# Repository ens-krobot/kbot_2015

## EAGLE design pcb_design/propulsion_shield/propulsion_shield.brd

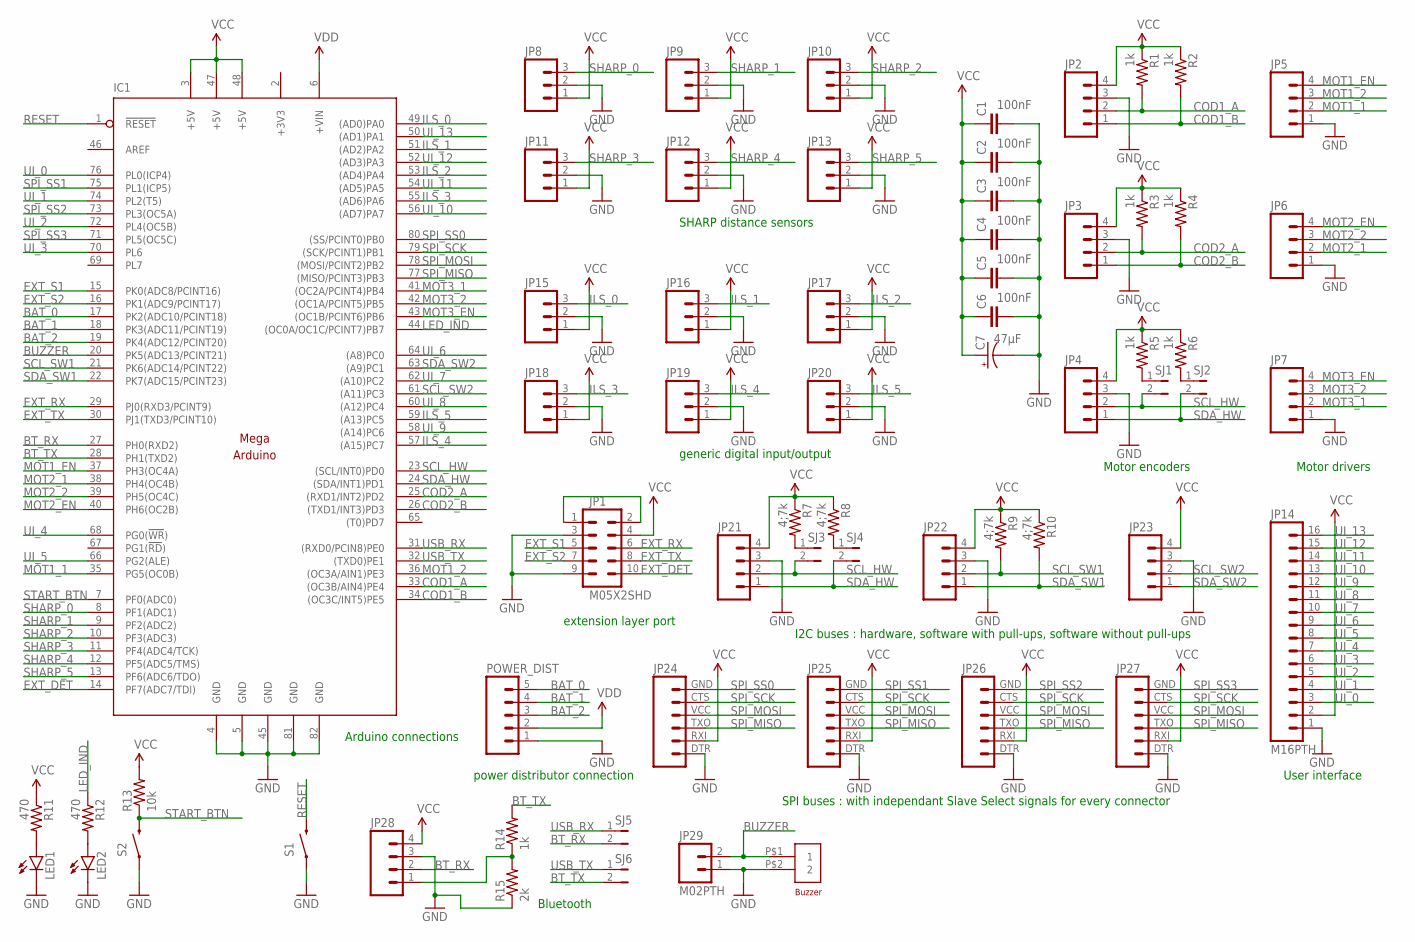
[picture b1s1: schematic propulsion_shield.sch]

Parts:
C1, C2, C3, C4, C5, C6: 100nF; 1206
C7: 47µF; PANASONIC_D
IC1: MEGAARDUINO_13; MEGA_ARDUINO_NO_HOLE
JP1: M05X2SHD; 2X5-SHROUDED
JP2, JP3, JP4, JP5, JP6, JP7, JP21, JP22, JP23, JP28: M04PTH; 1X04
JP8, JP9, JP10, JP11, JP12, JP13, JP15, JP16, JP17, JP18, JP19, JP20: M03PTH; 1X03
JP14: M16PTH; 1X16
JP24, JP25, JP26, JP27: M06SIP; 1X06
JP29: M02PTH; 1X02
LED1, LED2: LED1206; LED-1206
POWER_DIST: M05PTH; 1X05
R1, R2, R3, R4, R5, R6, R14: 1k; 1206
R7, R8, R9, R10: 4;7k; 1206
R11, R12: 470; 1206
R13: 10k; 1206
R15: 2k; 1206
S1, S2: SWITCH-MOMENTARY-2PTH; TACTILE-PTH
SJ1, SJ2, SJ3, SJ4, SJ5, SJ6: JUMPER-PTH-2-NO; PTH-JUMPER-2-NO_NO_SILK
U$1: BUZZER

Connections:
+3V3: IC1.2 (+3V3)
BAT_0: IC1.17 (PK2(ADC10/PCINT18)), POWER_DIST.5
BAT_1: IC1.18 (PK3(ADC11/PCINT19)), POWER_DIST.4
BAT_2: IC1.19 (PK4(ADC12/PCINT20)), POWER_DIST.3
BT_RX: IC1.27 (PH0(RXD2)), JP28.2, SJ5.2
BT_TX: IC1.28 (PH1(TXD2)), R14.2, SJ6.2
BUZZER: IC1.20 (PK5(ADC13/PCINT21)), JP29.2, U$1.P$1 (1)
COD1_A: IC1.33 ((OC3B/AIN4)PE4), JP2.2, R1.2
COD1_B: IC1.34 ((OC3C/INT5)PE5), JP2.1, R2.2
COD2_A: IC1.25 ((RXD1/INT2)PD2), JP3.2, R3.2
COD2_B: IC1.26 ((TXD1/INT3)PD3), JP3.1, R4.2
EXT_DET: IC1.14 (PF7(ADC7/TDI)), JP1.10
EXT_RX: IC1.29 (PJ0(RXD3/PCINT9)), JP1.6
EXT_S1: IC1.15 (PK0(ADC8/PCINT16)), JP1.5
EXT_S2: IC1.16 (PK1(ADC9/PCINT17)), JP1.7
EXT_TX: IC1.30 (PJ1(TXD3/PCINT10)), JP1.8
GND: C1.2, C2.2, C3.2, C4.2, C5.2, C6.2, C7.-, IC1.4 (GND), IC1.5 (GND), IC1.45 (GND), IC1.81 (GND), IC1.82 (GND), JP1.3, JP1.9, JP2.3, JP3.3, JP4.3, JP5.1, JP6.1, JP7.1, JP8.2, JP9.2, JP10.2, JP11.2, JP12.2, JP13.2, JP14.1, JP15.2, JP16.2, JP17.2, JP18.2, JP19.2, JP20.2, JP21.3, JP22.3, JP23.3, JP24.DTR (1), JP25.DTR (1), JP26.DTR (1), JP27.DTR (1), JP28.3, JP29.1, LED1.C, LED2.C, POWER_DIST.1, R15.1, S1.1, S2.1, U$1.P$2 (2)
ILS_0: IC1.49 ((AD0)PA0), JP15.3
ILS_1: IC1.51 ((AD2)PA2), JP16.3
ILS_2: IC1.53 ((AD4)PA4), JP17.3
ILS_3: IC1.55 ((AD6)PA6), JP18.3
ILS_4: IC1.57 ((A15)PC7), JP19.3
ILS_5: IC1.59 ((A13)PC5), JP20.3
LED_IND: IC1.44 ((OC0A/OC1C/PCINT7)PB7), R12.1
MOT1_1: IC1.35 (PG5(OC0B)), JP5.2
MOT1_2: IC1.36 ((OC3A/AIN1)PE3), JP5.3
MOT1_EN: IC1.37 (PH3(OC4A)), JP5.4
MOT2_1: IC1.38 (PH4(OC4B)), JP6.2
MOT2_2: IC1.39 (PH5(OC4C)), JP6.3
MOT2_EN: IC1.40 (PH6(OC2B)), JP6.4
MOT3_1: IC1.41 ((OC2A/PCINT4)PB4), JP7.2
MOT3_2: IC1.42 ((OC1A/PCINT5)PB5), JP7.3
MOT3_EN: IC1.43 ((OC1B/PCINT6)PB6), JP7.4
unnamed: JP1.1, JP1.2
unnamed: R7.2, SJ3.1
unnamed: R8.2, SJ4.1
unnamed: R5.2, SJ1.1
unnamed: R6.2, SJ2.1
unnamed: LED1.A, R11.2
unnamed: LED2.A, R12.2
unnamed: JP28.1, R14.1, R15.2
RESET: IC1.1 (!RESET), S1.3 (2)
SCL_HW: IC1.23 ((SCL/INT0)PD0), JP4.2, JP21.2, SJ1.2, SJ3.2
SCL_SW1: IC1.21 (PK6(ADC14/PCINT22)), JP22.2, R9.2
SCL_SW2: IC1.61 ((A11)PC3), JP23.2
SDA_HW: IC1.24 ((SDA/INT1)PD1), JP4.1, JP21.1, SJ2.2, SJ4.2
SDA_SW1: IC1.22 (PK7(ADC15/PCINT23)), JP22.1, R10.2
SDA_SW2: IC1.63 ((A9)PC1), JP23.1
SHARP_0: IC1.8 (PF1(ADC1)), JP8.3
SHARP_1: IC1.9 (PF2(ADC2)), JP9.3
SHARP_2: IC1.10 (PF3(ADC3)), JP10.3
SHARP_3: IC1.11 (PF4(ADC4/TCK)), JP11.3
SHARP_4: IC1.12 (PF5(ADC5/TMS)), JP12.3
SHARP_5: IC1.13 (PF6(ADC6/TDO)), JP13.3
SPI_MISO: IC1.77 ((MISO/PCINT3)PB3), JP24.TXO (3), JP25.TXO (3), JP26.TXO (3), JP27.TXO (3)
SPI_MOSI: IC1.78 ((MOSI/PCINT2)PB2), JP24.VCC (4), JP25.VCC (4), JP26.VCC (4), JP27.VCC (4)
SPI_SCK: IC1.79 ((SCK/PCINT1)PB1), JP24.CTS (5), JP25.CTS (5), JP26.CTS (5), JP27.CTS (5)
SPI_SS0: IC1.80 ((SS/PCINT0)PB0), JP24.GND (6)
SPI_SS1: IC1.75 (PL1(ICP5)), JP25.GND (6)
SPI_SS2: IC1.73 (PL3(OC5A)), JP26.GND (6)
SPI_SS3: IC1.71 (PL5(OC5C)), JP27.GND (6)
START_BTN: IC1.7 (PF0(ADC0)), R13.1, S2.3 (2)
UI_0: IC1.76 (PL0(ICP4)), JP14.3
UI_1: IC1.74 (PL2(T5)), JP14.4
UI_2: IC1.72 (PL4(OC5B)), JP14.5
UI_3: IC1.70 (PL6), JP14.6
UI_4: IC1.68 (PG0(!WR!)), JP14.7
UI_5: IC1.66 (PG2(ALE)), JP14.8
UI_6: IC1.64 ((A8)PC0), JP14.9
UI_7: IC1.62 ((A10)PC2), JP14.10
UI_8: IC1.60 ((A12)PC4), JP14.11
UI_9: IC1.58 ((A14)PC6), JP14.12
UI_10: IC1.56 ((AD7)PA7), JP14.13
UI_11: IC1.54 ((AD5)PA5), JP14.14
UI_12: IC1.52 ((AD3)PA3), JP14.15
UI_13: IC1.50 ((AD1)PA1), JP14.16
USB_RX: IC1.31 ((RXD0/PCIN8)PE0), SJ5.1
USB_TX: IC1.32 ((TXD0)PE1), SJ6.1
VCC: C1.1, C2.1, C3.1, C4.1, C5.1, C6.1, C7.+, IC1.3 (+5V), IC1.47 (+5V), IC1.48 (+5V), JP1.4, JP2.4, JP3.4, JP4.4, JP8.1, JP9.1, JP10.1, JP11.1, JP12.1, JP13.1, JP14.2, JP15.1, JP16.1, JP17.1, JP18.1, JP19.1, JP20.1, JP21.4, JP22.4, JP23.4, JP24.RXI (2), JP25.RXI (2), JP26.RXI (2), JP27.RXI (2), JP28.4, R1.1, R2.1, R3.1, R4.1, R5.1, R6.1, R7.1, R8.1, R9.1, R10.1, R11.1, R13.2
VDD: IC1.6 (+VIN), POWER_DIST.2

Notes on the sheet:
power distributor connection
extension layer port
Arduino connections
Motor encoders
Motor drivers
User interface
SHARP distance sensors
generic digital input/output
I2C buses : hardware, software with pull-ups, software without pull-ups
SPI buses : with independant Slave Select signals for every connector
Bluetooth

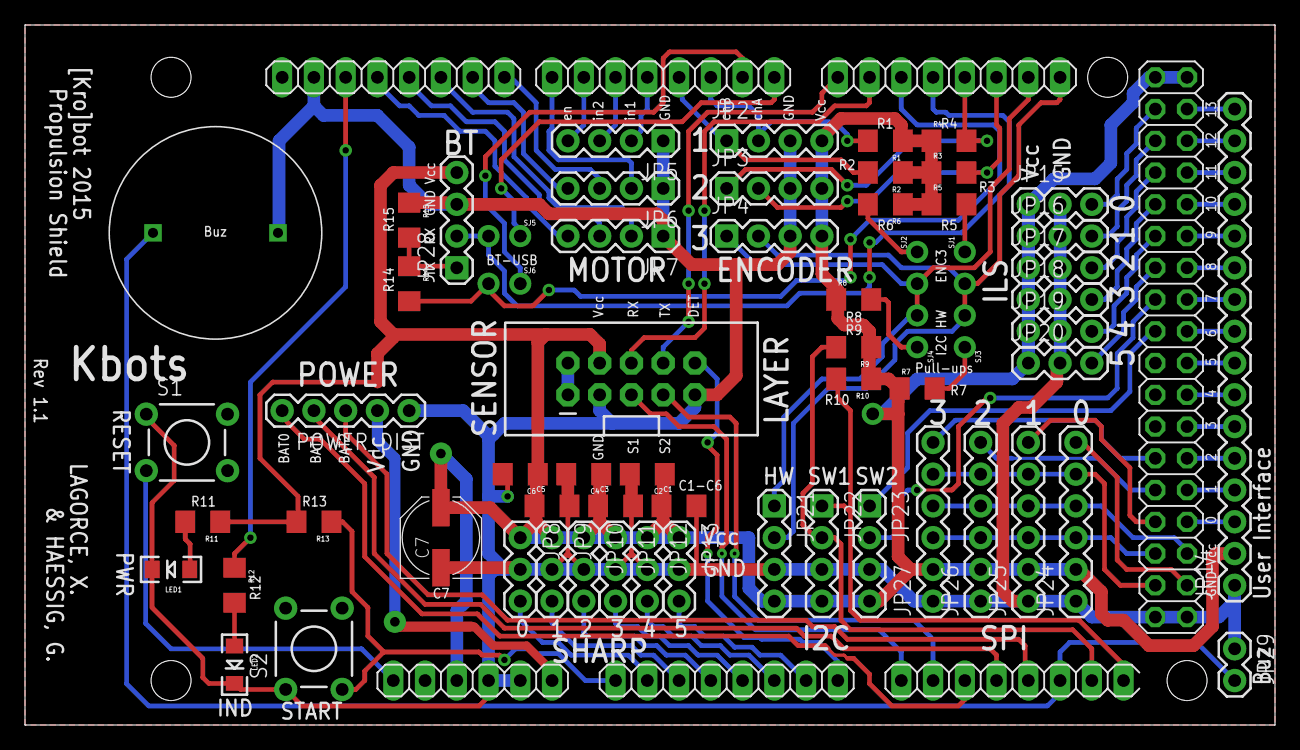
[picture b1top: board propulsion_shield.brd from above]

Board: 2 copper layers, 100.0 x 56.0 mm, 64 parts (0 on the bottom side), 79 nets.

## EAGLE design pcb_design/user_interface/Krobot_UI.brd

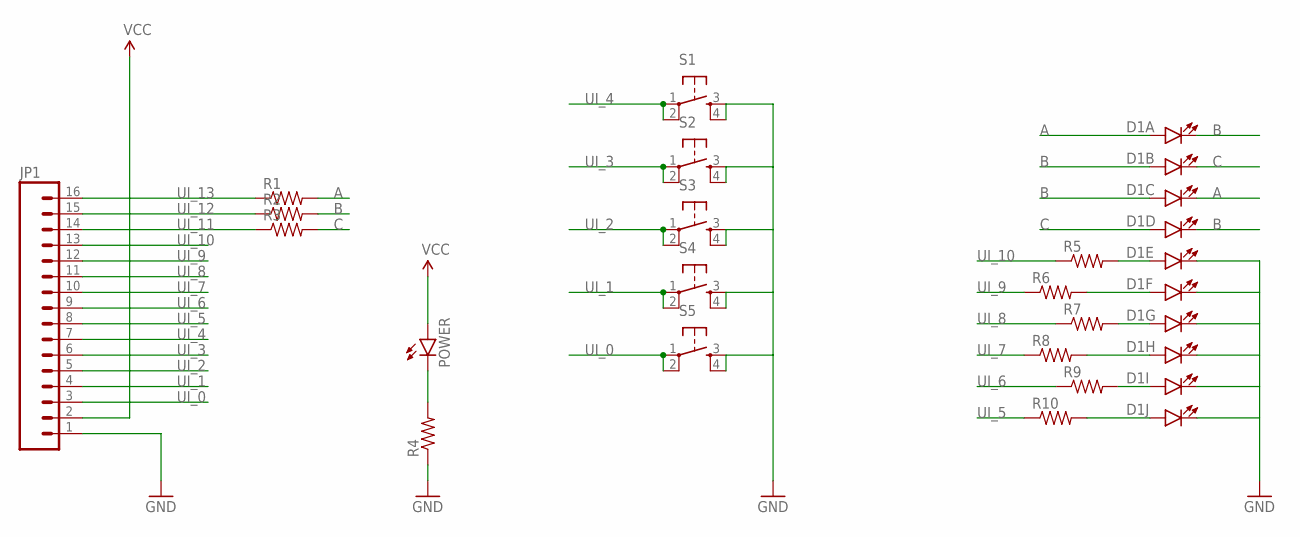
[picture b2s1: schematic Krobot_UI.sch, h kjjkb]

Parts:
D1: LED_BARGRAPH_10; LED_BARGAPH_10
JP1: 1X16_LONGPADS
POWER: LED1206; LED-1206
R1, R2, R3, R4, R5, R6, R7, R8, R9, R10: RESISTOR1206; 1206
S1, S2, S3, S4, S5: TAC_SWITCHPTH; TACTILE-PTH

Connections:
A: D1.1 (A), D1.18 (C), R1.2
B: D1.2 (A), D1.3 (A), D1.17 (C), D1.20 (C), R2.2
C: D1.4 (A), D1.19 (C), R3.2
GND: D1.11 (C), D1.12 (C), D1.13 (C), D1.14 (C), D1.15 (C), D1.16 (C), JP1.1, R4.1, S1.3, S1.4, S2.3, S2.4, S3.3, S3.4, S4.3, S4.4, S5.3, S5.4
unnamed: D1.5 (A), R5.2
unnamed: D1.6 (A), R6.2
unnamed: D1.7 (A), R7.2
unnamed: D1.8 (A), R8.2
unnamed: D1.9 (A), R9.2
unnamed: D1.10 (A), R10.2
unnamed: POWER.C, R4.2
UI_0: JP1.3, S5.1, S5.2
UI_1: JP1.4, S4.1, S4.2
UI_2: JP1.5, S3.1, S3.2
UI_3: JP1.6, S2.1, S2.2
UI_4: JP1.7, S1.1, S1.2
UI_5: JP1.8, R10.1
UI_6: JP1.9, R9.1
UI_7: JP1.10, R8.1
UI_8: JP1.11, R7.1
UI_9: JP1.12, R6.1
UI_10: JP1.13, R5.1
UI_11: JP1.14, R3.1
UI_12: JP1.15, R2.1
UI_13: JP1.16, R1.1
VCC: JP1.2, POWER.A

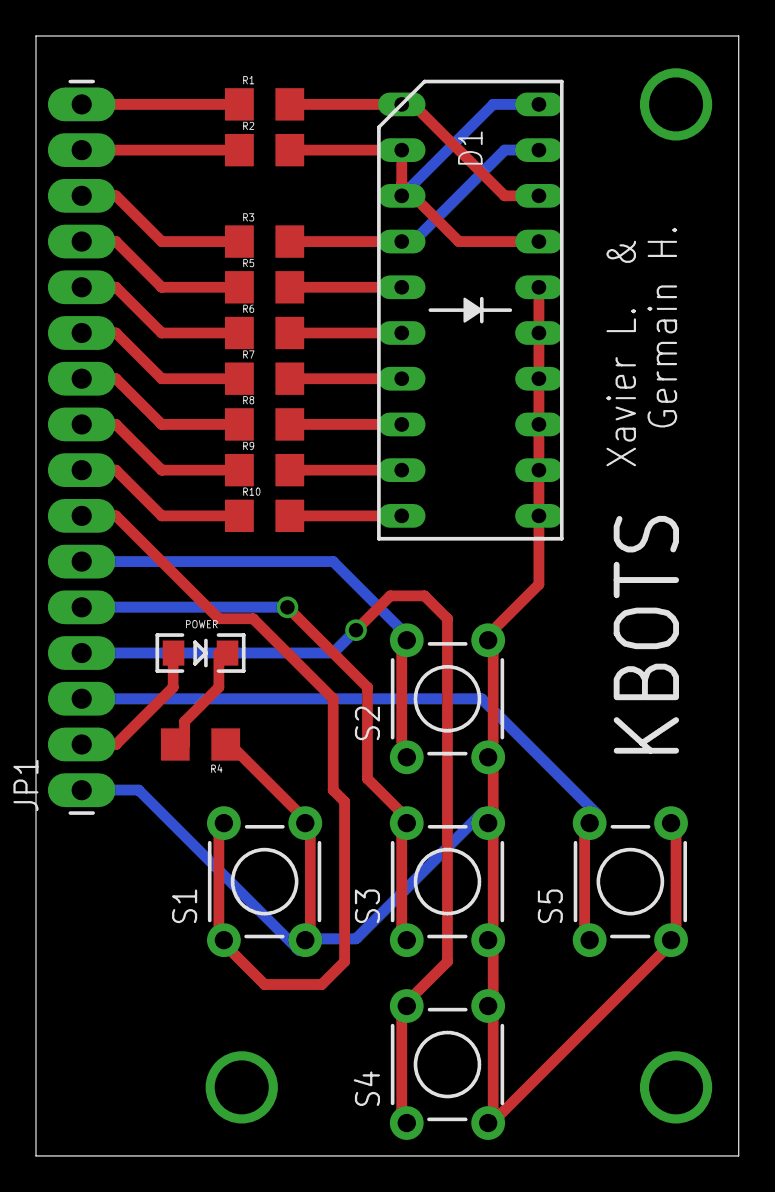
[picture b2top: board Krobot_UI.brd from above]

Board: 2 copper layers, 39.0 x 62.2 mm, 18 parts (0 on the bottom side), 26 nets.

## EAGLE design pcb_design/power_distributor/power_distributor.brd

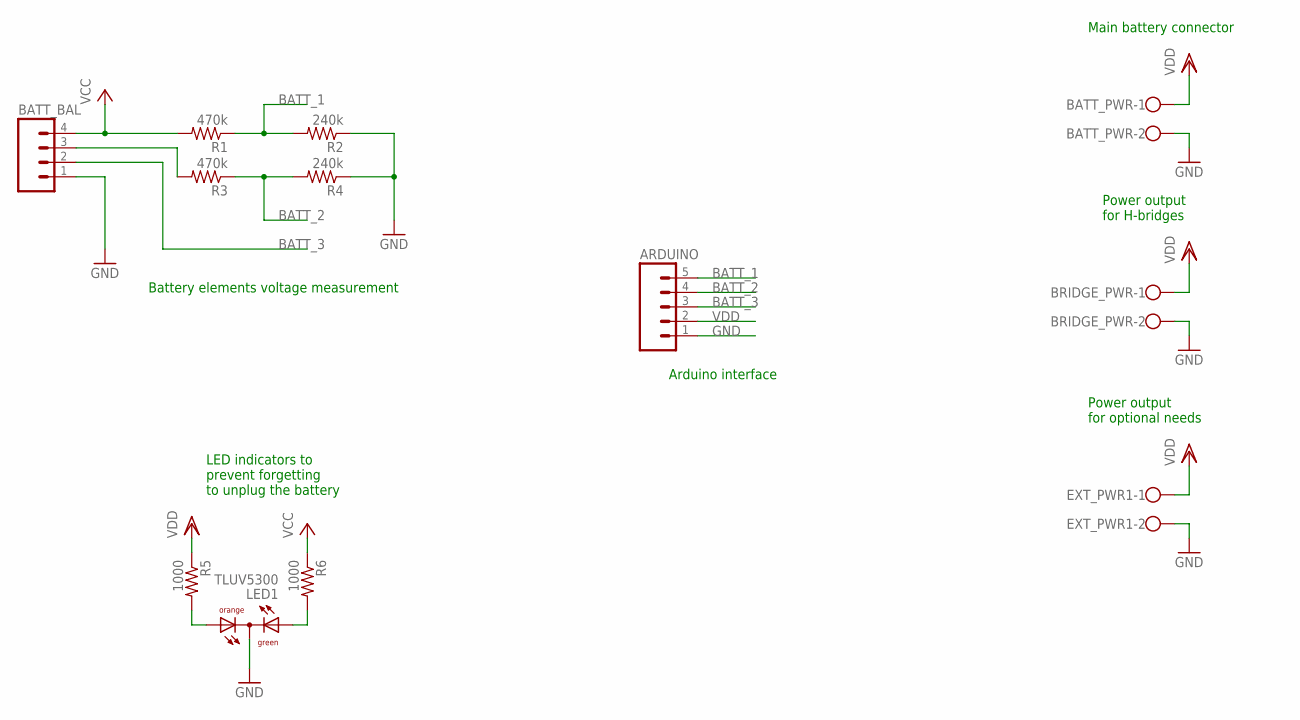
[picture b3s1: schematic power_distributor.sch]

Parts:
ARDUINO: M05PTH; 1X05
BATT_BAL: M04POLAR; MOLEX-1X4
BATT_PWR: W237-102
BRIDGE_PWR: W237-102
EXT_PWR1: W237-102
LED1: TLUV5300
R1, R3: 470k; 1206
R2, R4: 240k; 1206
R5, R6: 1000; 1206

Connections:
BATT_1: ARDUINO.5, R1.1, R2.2
BATT_2: ARDUINO.4, R3.1, R4.2
BATT_3: ARDUINO.3, BATT_BAL.2
GND: ARDUINO.1, BATT_BAL.1, BATT_PWR.2, BRIDGE_PWR.2, EXT_PWR1.2, LED1.CC, R2.1, R4.1
unnamed: LED1.AO, R5.2
unnamed: BATT_BAL.3, R3.2
unnamed: LED1.AG, R6.2
VCC: BATT_BAL.4, R1.2, R6.1
VDD: ARDUINO.2, BATT_PWR.1, BRIDGE_PWR.1, EXT_PWR1.1, R5.1

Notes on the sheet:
Main battery connector
LED indicators to prevent forgetting to unplug the battery
Power output for H-bridges
Power output for optional needs
Arduino interface
Battery elements voltage measurement

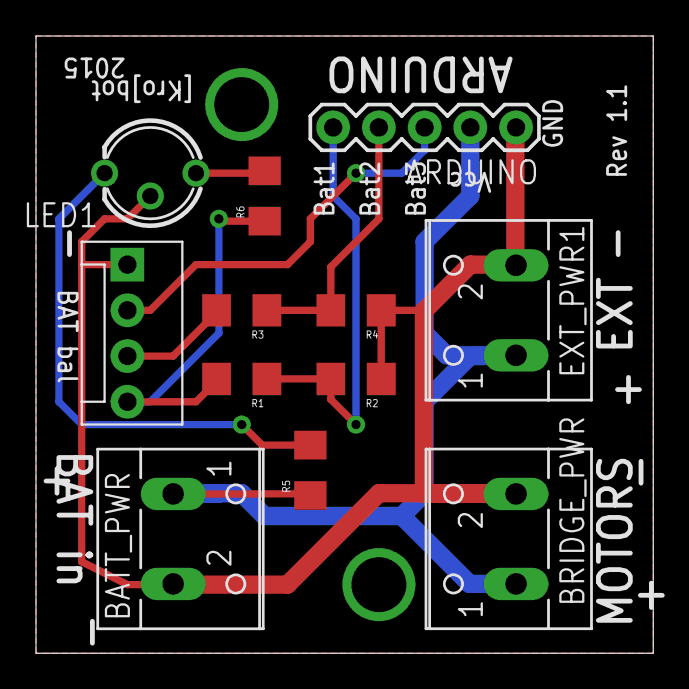
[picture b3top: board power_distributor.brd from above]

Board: 2 copper layers, 34.3 x 34.3 mm, 12 parts (0 on the bottom side), 9 nets.

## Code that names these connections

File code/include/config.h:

/************************************************************************
 * File : config.h                                                      *
 *  Configuration file for Kbots main shield.                           *
 *                                                                      *
 * Copyright : (c) 2014, Germain Haessig <ghaessig@crans.org>           *
 * Copyright : (c) 2014, Xavier Lagorce <Xavier.Lagorce@crans.org>      *
 ************************************************************************/

// Only include this file once
#ifndef __CONFIG_H
#define __CONFIG_H

/* ---------------- 
  MOTORS pinout
---------------- */
#define MOT1_1 4
#define MOT1_2 5
#define COD1_A 2
#define COD1_B 3
#define MOT1_EN 6

#define MOT2_1 7
#define MOT2_2 8
#define COD2_A 19
#define COD2_B 18
#define MOT2_EN 9

#define MOT3_1 10
#define MOT3_2 11
#define COD3_A 21
#define COD3_B 20
#define MOT3_EN 12


/* ------------ 
  IR Sensor
------------ */
#define SHARP_0 A1
#define SHARP_1 A2
#define SHARP_2 A3
#define SHARP_3 A4
#define SHARP_4 A5
#define SHARP_5 A6


/* -------------------- 
  BATTERY monitoring
-------------------- */
#define BATT_0 A10
#define BATT_1 A11
#define BATT_2 A12


/* ----------------
  COMMUNICATION
---------------- */
#define SCL_SW1 A14
#define SDA_SW1 A15

#define SCL_SW2 34
#define SDA_SW2 36

#define EXT_TX 14 //TX3
#define EXT_RX 15 //RX3

#define BT_RX 17
#define BT_TX 16

#define SPI_MOSI 51
#define SPI_MISO 50
#define SPI_SCK 42
#define SPI_SS0 53
#define SPI_SS1 48
#define SPI_SS2 46
#define SPI_SS3 44


/* ------------ 
  ILS pinout
------------ */
#define ILS_0 22
#define ILS_1 24
#define ILS_2 26
#define ILS_3 28
#define ILS_4 30
#define ILS_5 32


/* --------------------------------
  USER INTERFACE dedicated pins 
-------------------------------- */
#define UI_LED_CPA 23 //Charlieplexing A
#define UI_LED_CPB 25 //Charlieplexing B
#define UI_LED_CPC 27 //Charlieplexing C
#define UI_LED5 29
#define UI_LED4 31
#define UI_LED3 33
#define UI_LED2 35
#define UI_LED1 37
#define UI_LED0 39
#define UI_BTN_DOWN 41
#define UI_BTN_LEFT 43
#define UI_BTN_CENTER 45
#define UI_BTN_RIGHT 47
#define UI_BTN_UP 49


/* -------- 
  OTHERS
-------- */
#define LED_IND 13
#define EXT_DET A7
#define EXT_S1 A8
#define EXT_S2 A9
#define START_BTN A0
#define BUZZER A13

#endif

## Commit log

2014-10-03 [git] Ignore eagle history files
2014-10-03 [pcb_design] Added some support files
    * Arduino PCB library
    * DRU file for electrodragon
2014-10-03 [pcb_design] Initial import of the power distributor board
2014-10-05 [propulsion_shield] Added first drawft of pinout for the shield
2014-10-06 [propulsion_shield] Improved pinout description
2014-10-07 [support_files] Added new footprint for arduino mega and make git ignore library editing temp files
2014-10-07 [propulsion_shield] Added schematics and "empty" board for propulsion shield
2014-10-07 [propulsion_shield] First draft of components placement + Bugfixes in schematics
2014-10-08 [propulsion_shield] Full routing of the PCB
2014-10-08 [propulsion_shield] Updated pinout documentation according to last version of schematics
2014-10-08 [propulsion_shield] Added Silkscreen on board
2014-10-09 [propulsion_shield] Added a buzzer on the board
2014-10-27 [code/include] Add pinout file (config.h) for propulsion shield
2014-10-27 [user_interface] Add user_interface board design
2014-11-06 [code] Changed a few naming conventions in config.h + reformat
2014-11-17 [code] Initial import of the KbotsLib + simple example
2015-02-11 [code] Adapted Odometry and Propulsion classes to allow omnidirectional robots
2015-05-12 [SimpleScheduler] Added reset facilities to chronos
2015-05-12 [SpeedProfiler] Added member function de stop the robot with a given acceleration
2015-05-12 [libraries] Added liquidcrystal library with support for software I2C
2015-10-07 [PCB/propulsion_shield] Correction routing of power supply to Vin arduino pin (schematics + PCB)
2015-10-08 [PCB/power_distributor] Correcting wrong JST footprint
2015-10-08 [PCB/krobot_ui] Change date on silkscreen
2015-10-08 [PCB/propulsion_shield] Change date and version number

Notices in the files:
parts and their libraries:
SparkFun-Connectors: Licensing: Creative Commons ShareAlike 4.0 International - https://creativecommons.org/licenses/by-sa/4.0
